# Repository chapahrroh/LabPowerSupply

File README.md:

# LabPowerSupply
fuente de poder para laboratorio, tomando como base una fuente de poder ATX de 1000 W dell

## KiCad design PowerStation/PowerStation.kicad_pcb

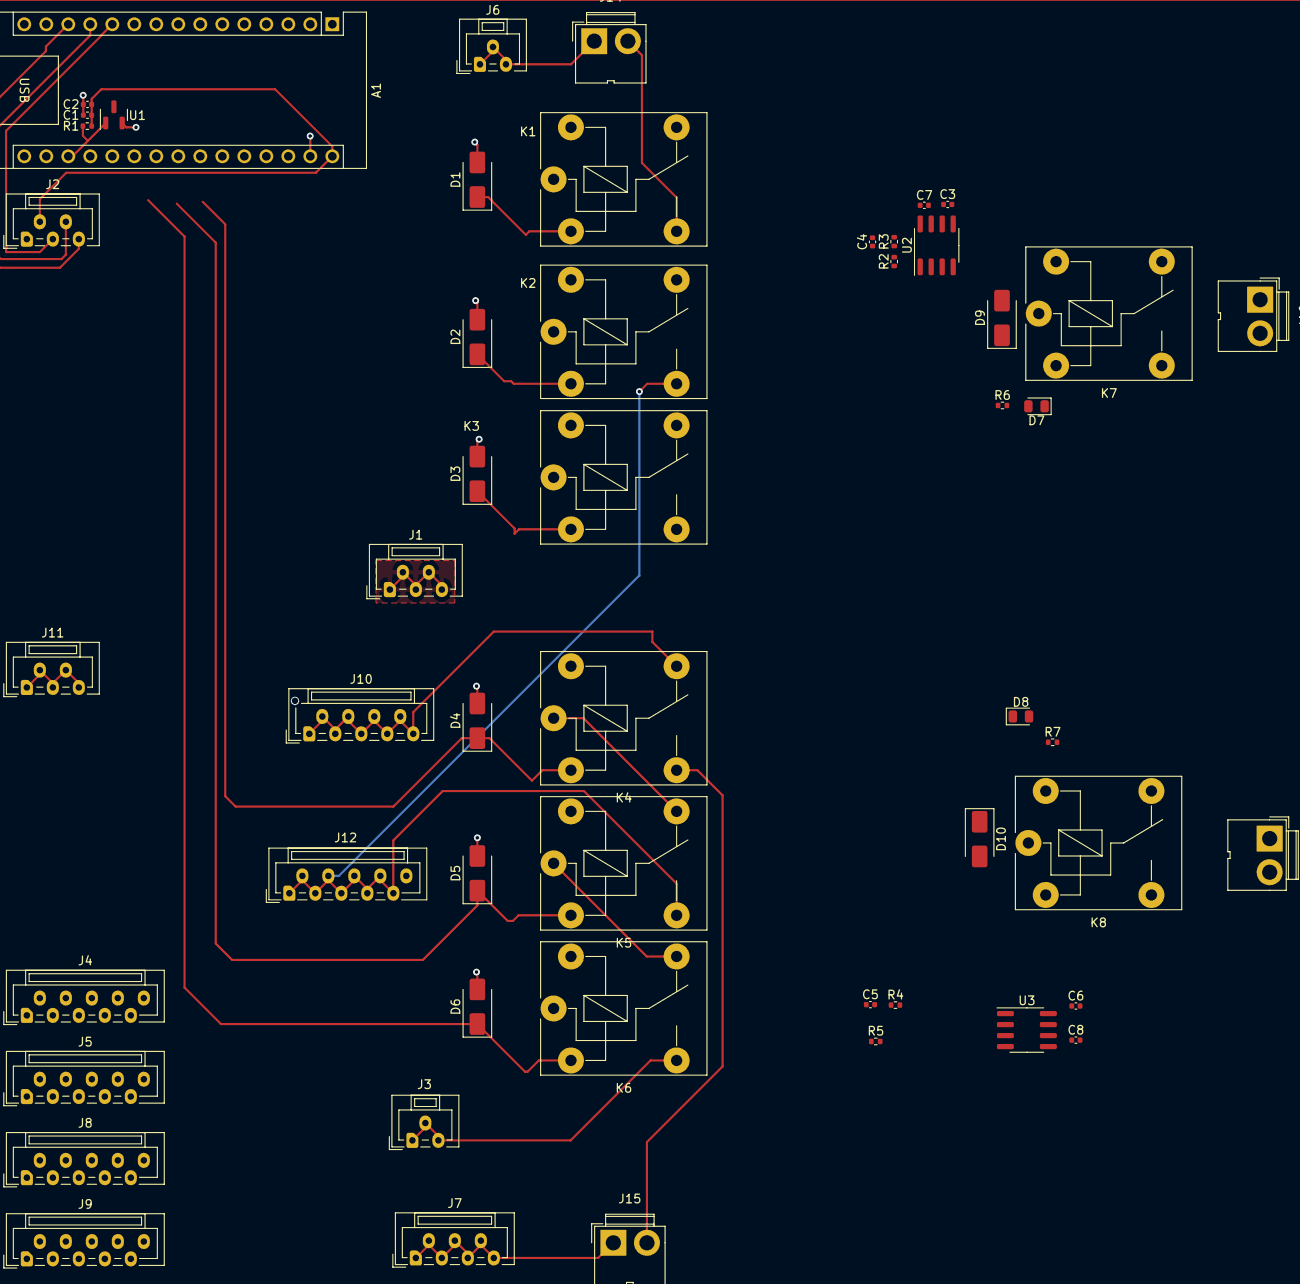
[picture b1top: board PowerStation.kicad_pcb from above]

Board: 2 copper layers, 53 parts (0 on the bottom side), 41 nets.

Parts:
A1: Arduino_Nano_v3.x; Arduino_Nano
C1: 0.1 uF; C_0402_1005Metric
C2: 10 uF; C_0402_1005Metric
C3: 1nF; C_0402_1005Metric
C4, C5: 100nF; C_0402_1005Metric
C6: 1nf; C_0402_1005Metric
C7, C8: 10nF; C_0402_1005Metric
D1, D2, D3, D4, D5, D6, D9, D10: 1N4007; D_SMA
D7, D8: LED; LED_0805_2012Metric
J1: 12VA; JST_ZE_B05B-ZESK-D_1x05_P1.50mm_Vertical
J2: control; JST_ZE_B05B-ZESK-D_1x05_P1.50mm_Vertical
J3: 12VB; JST_ZE_B03B-ZESK-D_1x03_P1.50mm_Vertical
J4, J5, J8, J9: GND; JST_ZE_B10B-ZESK-D_1x10_P1.50mm_Vertical
J6: 12VC; JST_ZE_B03B-ZESK-D_1x03_P1.50mm_Vertical
J7: 12VD; JST_ZE_B07B-ZESK-D_1x07_P1.50mm_Vertical
J10: 5V; JST_ZE_B09B-ZESK-1D_1x09_P1.50mm_Vertical
J11: 12VE; JST_ZE_B05B-ZESK-D_1x05_P1.50mm_Vertical
J12: 3V3; JST_ZE_B10B-ZESK-D_1x10_P1.50mm_Vertical
J13: Salida 2; JWT_A3963_1x02_P3.96mm_Vertical
J14, J15: ReguladorExterno; JWT_A3963_1x02_P3.96mm_Vertical
J16: Salida 1; JWT_A3963_1x02_P3.96mm_Vertical
K1, K2, K3, K4, K5, K6, K7, K8: Relay_SPDT; Relay_SPDT_Finder_36.11
R1: 909 ohm; R_0402_1005Metric
R2, R4: 1M ohm; R_0402_1005Metric
R3, R5: 100K ohm; R_0402_1005Metric
R6, R7: 330; R_0402_1005Metric
U1: LM4040DBZ-4.1; SOT-23
U2, U3: ACS712xLCTR-20A; SOIC-8_3.9x4.9mm_P1.27mm

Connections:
/control de salidas/3V3: J12.1, J12.2, J12.3, J12.4, J12.5, J12.6, J12.7, J12.8, J12.9, K2.14, K5.14
/control de salidas/5V: J10.1, J10.2, J10.3, J10.4, J10.5, J10.6, J10.7, J10.8, J10.9, K1.12, K4.12
/control de salidas/12VA: J1.1, J1.2, J1.3, J1.4, J1.5, K3.14
/control de salidas/12VB: J3.1, J3.2, J3.3, K6.14
/control de salidas/12VC: J6.1, J6.2, J6.3, J14.1
/control de salidas/12VD: J7.1, J7.2, J7.3, J7.4, J7.5, J7.6, J7.7, J15.1
/control de salidas/Reguladr de voltaje 1/SalidaRegulada2: J14.2, K1.14
/control de salidas/Reguladr de voltaje 2/SalidaRegulada2: J15.2, K4.14
/control de salidas/relay1S1: A1.5 (D2), D1.1 (K), K1.A1
/control de salidas/relay1S2: A1.8 (D5), D4.1 (K), K4.A1
/control de salidas/relay2S1: A1.6 (D3), D2.1 (K), K2.A1
/control de salidas/relay2S2: A1.9 (D6), D5.1 (K), K5.A1
/control de salidas/relay3S1: A1.7 (D4), D3.1 (K), K3.A1
/control de salidas/relay3S2: A1.10 (D7), D6.1 (K), K6.A1
/control/5V: A1.30 (VIN), C1.1, C2.1, C7.1, C8.1, J2.2, R1.1, U2.8 (VCC), U3.8 (VCC)
/control/AREF: A1.18 (AREF), R1.2, U1.1 (K)
/control/analogIN1: A1.19 (A0), C4.1, R2.2, R3.1
/control/analogIN2: A1.20 (A1), U2.7 (VIOUT)
/control/analogIN3: A1.21 (A2), C5.1, R4.2, R5.1
/control/analogIN4: A1.22 (A3), U3.7 (VIOUT)
/control/digitalPin7: A1.11 (D8), J2.3
/control/digitalPin8: A1.12 (D9), J2.4
/control/digitalPin9: A1.13 (D10), J2.5
/control/digitalPin10: A1.14 (D11), D9.1 (K), K7.A2, R6.1
/control/digitalPin11: A1.15 (D12), D10.1 (K), K8.A2, R7.1
/entrada de fuente/12VE: J11.1, J11.2, J11.3, J11.4, J11.5
/medicion de salidas/Entrada1: R2.1, U2.1 (IP+), U2.2 (IP+)
/medicion de salidas/Entrada2: R4.1, U3.1 (IP+), U3.2 (IP+)
/medicion de salidas/Salida1: K7.11, U2.3 (IP-), U2.4 (IP-)
/medicion de salidas/Salida2: K8.11, U3.3 (IP-), U3.4 (IP-)
GND: A1.4 (GND), A1.29 (GND), C1.2, C2.2, C3.2, C4.2, C5.2, C6.2, C7.2, C8.2, D1.2 (A), D2.2 (A), D3.2 (A), D4.2 (A), D5.2 (A), D6.2 (A), D7.1 (K), D8.1 (K), D9.2 (A), D10.2 (A), J4.1, J4.2, J4.3, J4.4, J4.5, J4.6, J4.7, J4.8, J4.9, J4.10, J5.1, J5.2, J5.3, J5.4, J5.5, J5.6, J5.7, J5.8, J5.9, J5.10, J8.1, J8.2, J8.3, J8.4, J8.5, J8.6, J8.7, J8.8, J8.9, J8.10, J9.1, J9.2, J9.3, J9.4, J9.5, J9.6, J9.7, J9.8, J9.9, J9.10, J13.1, J16.1, K1.A2, K2.A2, K3.A2, K4.A2, K5.A2, K6.A2, K7.A1, K8.A1, R3.2, R5.2, U1.2 (A), U2.5 (GND), U3.5 (GND)
unnamed: D7.2 (A), R6.2
unnamed: D8.2 (A), R7.2
unnamed: J13.2, K8.14
unnamed: J16.2, K7.14
unnamed: K1.11, K2.12
unnamed: K2.11, K3.12
unnamed: K4.11, K5.12
unnamed: K5.11, K6.12
unnamed: C3.1, U2.6 (FILTER)
unnamed: C6.1, U3.6 (FILTER)

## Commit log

2024-01-29 Primer Commit
2024-02-03 terminando diagrama
2024-02-03 esquema terminado
2024-02-05 added rust compilation
2024-02-05 test
2024-02-05 compilador estable para rust
2024-02-05 board test
2024-02-05 added gitignore
2024-02-10 entorno listo para compilar en rust
2024-02-11 avanxe en placa
2024-02-12 correccion de esquermatico y avanze en placa
2024-02-12 commit de test
2024-02-15 agregado diagrama y carpeta C
2024-02-15 preparado para compilacion en C
2024-02-15 correccion estructura de trbajo en C
2024-02-15 test rama rust
2024-02-15 test rama master
